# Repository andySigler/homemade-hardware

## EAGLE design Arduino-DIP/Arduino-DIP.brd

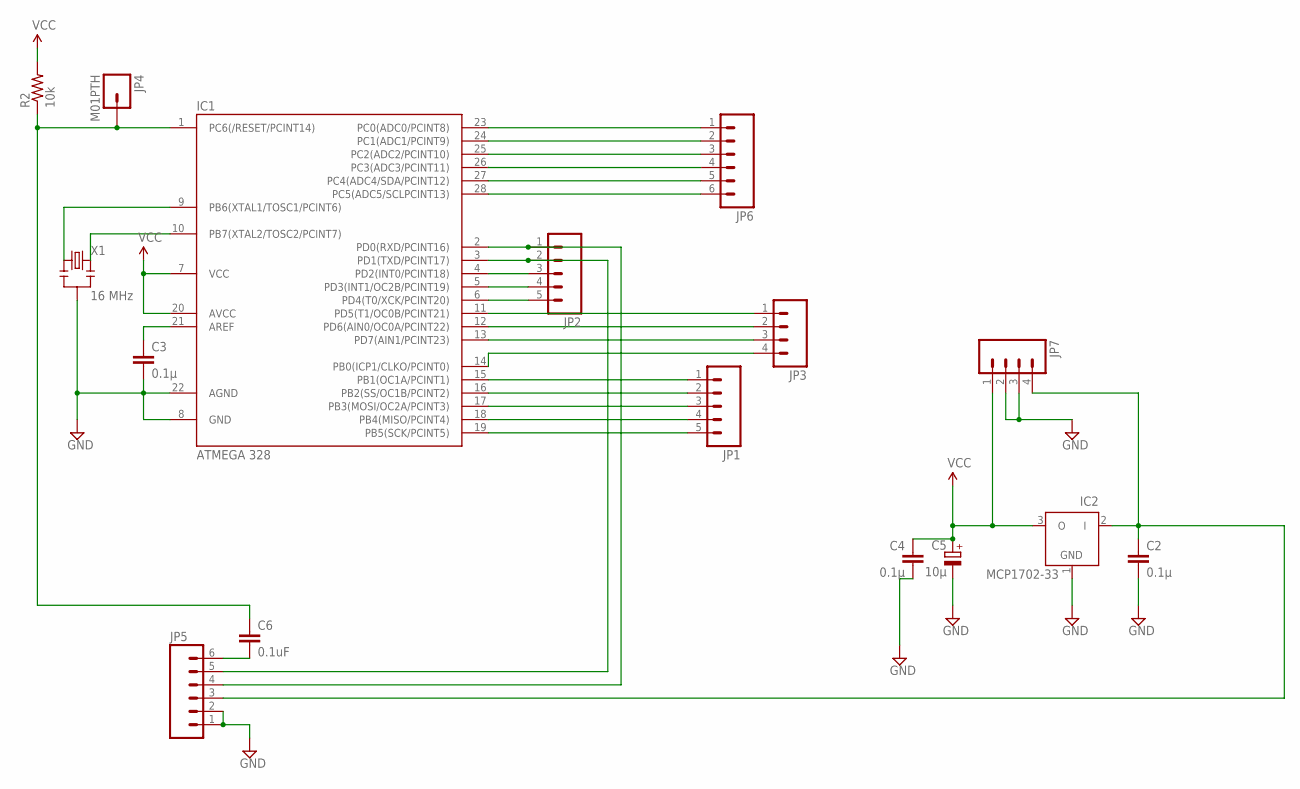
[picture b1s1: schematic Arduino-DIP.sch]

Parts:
C2, C3, C4: 0.1µ; C025-024X044
C5: 10µ; E1,8-4
C6: 0.1uF; CAP-PTH-5MM
IC1: ATMEGA 328; DIL28-3
IC2: MCP1702-33; TO92
JP1, JP2: M05PTH; 1X05
JP3, JP7: M04PTH; 1X04
JP4: M01PTH; 1X01
JP5, JP6: M06NO_SILK; 1X06_NO_SILK
R2: 10k; 1/6W-RES
X1: 16 MHz; RESONATOR-PTH

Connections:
GND: C2.2, C3.2, C4.2, C5.-, IC1.8 (GND), IC1.22 (AGND), IC2.1 (GND), JP5.1, JP5.2, JP7.2, JP7.3, X1.2
unnamed: IC1.9 (PB6(XTAL1/TOSC1/PCINT6)), X1.1
unnamed: IC1.23 (PC0(ADC0/PCINT8)), JP6.1
unnamed: IC1.24 (PC1(ADC1/PCINT9)), JP6.2
unnamed: IC1.25 (PC2(ADC2/PCINT10)), JP6.3
unnamed: IC1.26 (PC3(ADC3/PCINT11)), JP6.4
unnamed: IC1.27 (PC4(ADC4/SDA/PCINT12)), JP6.5
unnamed: IC1.28 (PC5(ADC5/SCLPCINT13)), JP6.6
unnamed: IC1.4 (PD2(INT0/PCINT18)), JP2.3
unnamed: IC1.5 (PD3(INT1/OC2B/PCINT19)), JP2.4
unnamed: IC1.6 (PD4(T0/XCK/PCINT20)), JP2.5
unnamed: IC1.11 (PD5(T1/OC0B/PCINT21)), JP3.1
unnamed: IC1.12 (PD6(AIN0/OC0A/PCINT22)), JP3.2
unnamed: IC1.13 (PD7(AIN1/PCINT23)), JP3.3
unnamed: IC1.14 (PB0(ICP1/CLKO/PCINT0)), JP3.4
unnamed: IC1.15 (PB1(OC1A/PCINT1)), JP1.1
unnamed: IC1.16 (PB2(SS/OC1B/PCINT2)), JP1.2
unnamed: IC1.17 (PB3(MOSI/OC2A/PCINT3)), JP1.3
unnamed: IC1.18 (PB4(MISO/PCINT4)), JP1.4
unnamed: C3.1, IC1.21 (AREF)
unnamed: C6.2, JP5.6
unnamed: IC1.10 (PB7(XTAL2/TOSC2/PCINT7)), X1.3
unnamed: IC1.19 (PB5(SCK/PCINT5)), JP1.5
PWR: C2.1, IC2.2 (I), JP5.3, JP7.4
RST: C6.1, IC1.1 (PC6(/RESET/PCINT14)), JP4.1, R2.1
RXD: IC1.2 (PD0(RXD/PCINT16)), JP2.1, JP5.4
TXD: IC1.3 (PD1(TXD/PCINT17)), JP2.2, JP5.5
VCC: C4.1, C5.+, IC1.7 (VCC), IC1.20 (AVCC), IC2.3 (O), JP7.1, R2.2

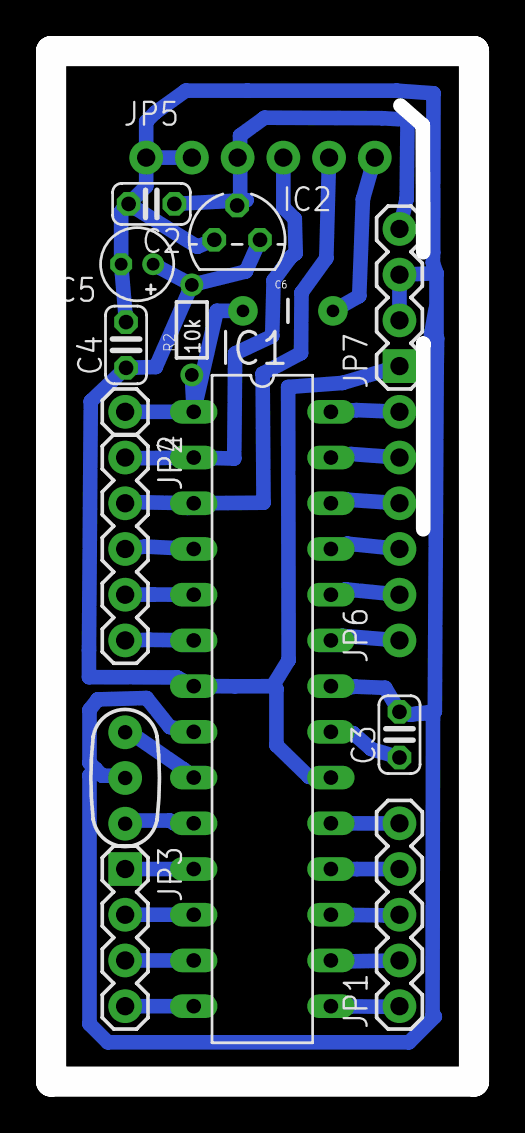
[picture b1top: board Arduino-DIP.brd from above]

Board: 2 copper layers, 23.5 x 57.3 mm, 16 parts (0 on the bottom side), 28 nets.

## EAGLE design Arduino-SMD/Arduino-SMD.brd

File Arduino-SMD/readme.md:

#Homemade SMD Microcontroller
##A clone of the Arduino-Pro-Mini

This is a redesign of the [Arduino Pro Mini](http://arduino.cc/en/Main/arduinoBoardProMini). The design is constrained by rapid prototyping tools and processes used to make the PCB. The most notabe constraints are micro-milling machines and DIY vias.

###Features

* Bootloader: Arduino Pro Mini (3.3V, 8MHz) w/ ATmega328
* Specs: 3.3 volts @ 8MHz
* Dimension: 3.5cm x 2cm (1.37" x 0.8")
* Onboard LED on Digital Pin 5 (not 13)
* FTDI programming headers
* Onboard reset button
* Solder points for [coin cell battery holder](http://www.digikey.com/product-detail/en/BA2032/BA2032-ND/257744)

###Pinouts

###Building

The board is designed to be milled on a micro-milling machine from copper clad plates. The job requires:
* 1/64" and 1/32" endmill to form routes
* 18 and 22 gauge drill bits for vias and holes
* 1/16" endmill for the dimension

Toolpath lines are drawn with the `wire` command on `.brd` layers `114`, `115`, `117`, and `118`.

Dynamask solder mask is then applied, and the board is exposed in a homemade UV lightbox for 45 seconds. This exposure is made through transparency film with the `.brd` `tStop` and `bStop` printed in black.

Vias are filled with solid 24 gauge wire, bent at 90 degree angles on either side to prevent them from falling out. Solder paste is then applied to the vias, and reflowed to make connections between the top and bottom.

###Parts List

* [ATMega328](http://www.digikey.com/product-detail/en/ATMEGA328-AUR/ATMEGA328-AURCT-ND/3440951) (this build does not use the more popular [ATMega328p](http://www.digikey.com/product-detail/en/ATMEGA328P-AUR/ATMEGA328P-AURCT-ND/3789455))
* [3.3 Volt Regulator](http://www.digikey.com/product-detail/en/MIC5205-3.3YM5%20TR/576-1259-1-ND/771886)
* [16 MHz Resonator](http://www.digikey.com/product-detail/en/PRQC16.00SR1010V00L/1253-1339-1-ND/4879394)
* [10 uF Pol. Capacitor](http://www.digikey.com/product-detail/en/T491A106K006AT7280/399-10116-1-ND/3759233) x 2
* [0.1 uF Capacitor](http://www.digikey.com/product-detail/en/CC0603ZRY5V9BB104/311-1343-1-ND/2103127) x 3
* [10,000 Ohm Resistor](http://www.digikey.com/product-detail/en/RC0603JR-0710KL/311-10KGRCT-ND/729647) x 3
* [LED](http://www.digikey.com/product-search/en?pv7=2&k=160-1434-2-ND&mnonly=0&newproducts=0&ColumnSort=0&page=1&quantity=0&ptm=0&fid=0&pageSize=25) x 2
* [Tactile Switch](http://www.digikey.com/product-detail/en/8-1437565-1/450-1941-ND/529677)
* [Coin Cell Battery Holder](http://www.digikey.com/product-detail/en/BA2032/BA2032-ND/257744) (optional)

###Burning a Bootloader

This build does not use the ATMega328p, but instead the ATMega328 because that's what I had on me. This will make the Arduino IDE unable to recognize the chip when burning a bootloader, but you can be fix it by adding a new device signature to the Arduino IDE's 'avrdude.conf' file.

The steps below will guide you through adding the device signature for the ATMega328. However, these changes must be undone in order to send sketches to the board after burning the bootloader.

#####Step 1
Quit the Arduino IDE if it is open.
#####Step 2
Find where you've installed Arduino, right-click it, and select `Show Package Contents`
#####Step 3
Navigate all the way into `Contents/Resources/Java/hardware/tools/avr/etc` and you'll find the `avrdude.conf` file
#####Step 4
Open `avrdude.conf` in a text editor, and find the following line for the ATMega328p:
```
signature   = 0x1e 0x95 0x0F;
```
#####Step 5
Comment that line out with an `#`, and add the new signature of the ATMega328. It should like like the following now:
```
# signature   = 0x1e 0x95 0x0F;
signature   = 0x1e 0x95 0x14;
```
#####Step 6
Restart the Arduino IDE, and you should be able to bootload the board.
#####Step 7
When you're done, change the `avrdude.conf` file back to it's original settings so that you can send your sketches to the board:
```
signature   = 0x1e 0x95 0x0F;
# signature   = 0x1e 0x95 0x14;
```

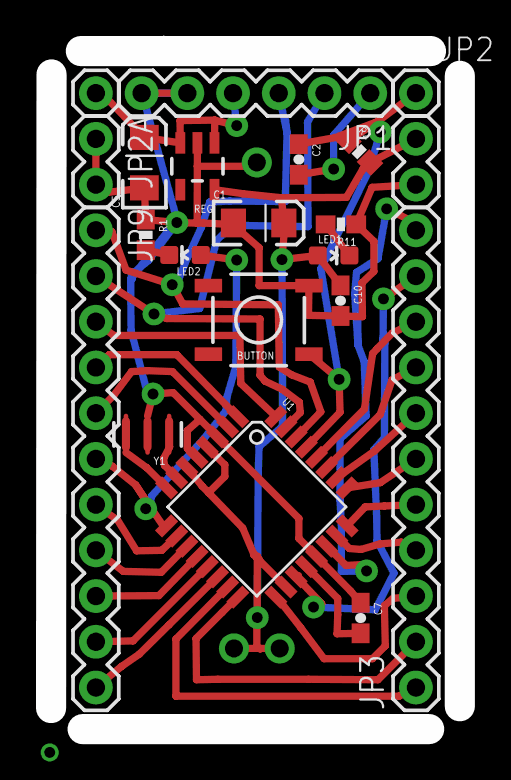
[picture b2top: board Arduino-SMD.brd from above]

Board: 2 copper layers, 22.7 x 37.7 mm, 22 parts (1 on the bottom side), 32 nets.

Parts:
BUTTON: Button; TACTILE-SWITCH-SMD
C1, C5: 10uF; EIA3216
C2, C7, C10: 0.1uF; 0603-CAP
JP1: FTDI Basic; 1X06
JP2, JP4: M01PTH; 1X01
JP2A, JP2A1: M02PTH; 1X02
JP3, JP9: M11PTH; 1X11
LED1, LED2: Red; 0603-LED-ALT1
R1, R2, R11: 10K; 0603-RES
REG: 3.3V; SOT23-5
U1: ATMEGA328P; TQFP32-08
U$1: BATTERY-ITP; BATTCOM_20MM_PTH
Y1: 8MHZ; RESONATOR-SMD

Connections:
DTR: C2.2, JP1.1
GND: BUTTON.3, C1.C, C5.C, C7.1, C10.2, JP1.5, JP1.6, JP2A.1, JP2A.2, JP2A1.2, R1.1, R11.1, REG.2, U1.3, U1.5, U1.21, U$1.GND, Y1.2
unnamed: U1.8, Y1.3
unnamed: U1.7, Y1.1
unnamed: LED1.C, R11.2
unnamed: JP3.1, U1.15
unnamed: JP3.2, U1.16
unnamed: JP3.3, U1.17
unnamed: JP3.11, U1.22
unnamed: JP3.10, U1.19
unnamed: JP3.9, U1.28
unnamed: JP3.8, U1.27
unnamed: JP3.7, U1.26
unnamed: JP3.6, U1.25
unnamed: JP3.5, U1.24
unnamed: JP3.4, U1.23
unnamed: LED2.C, R1.2
unnamed: JP9.7, U1.10
unnamed: C5.A, JP1.4, JP4.1, REG.1, REG.3
unnamed: JP9.3, U1.32
unnamed: C7.2, U1.20
unnamed: JP9.4, U1.1
unnamed: JP9.5, U1.2
unnamed: JP9.6, LED2.A, U1.9
unnamed: JP9.8, U1.11
unnamed: JP9.9, U1.12
unnamed: JP9.10, U1.13
unnamed: JP9.11, U1.14
RESET: BUTTON.1, C2.1, JP2.1, R2.1, U1.29
RXI: JP1.3, JP9.1, U1.30
TXO: JP1.2, JP9.2, U1.31
VCC: C1.A, C10.1, JP2A1.1, LED1.A, R2.2, REG.5, U1.4, U1.6, U1.18, U$1.PWR, U$1.PWR2

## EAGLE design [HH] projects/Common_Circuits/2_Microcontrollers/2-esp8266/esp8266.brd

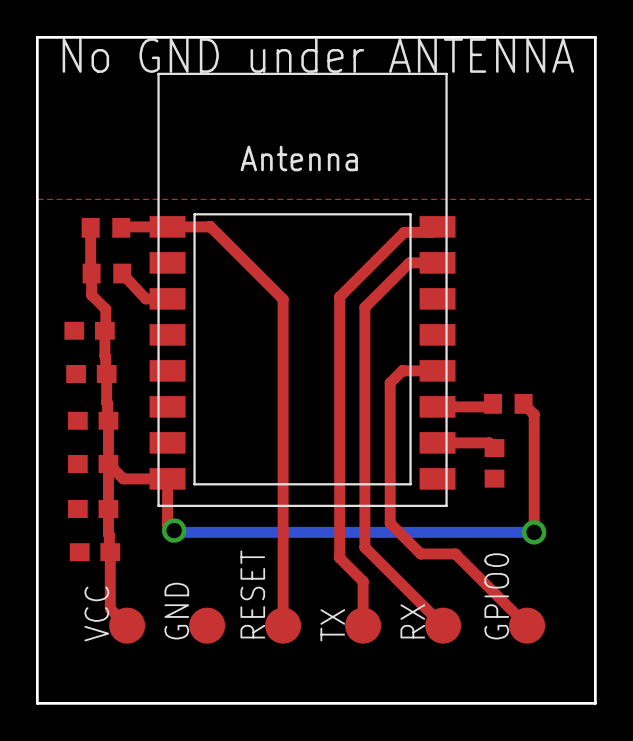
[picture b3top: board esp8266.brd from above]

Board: 2 copper layers, 31.0 x 37.0 mm, 17 parts (0 on the bottom side), 9 nets.

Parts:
C1, C6: 0.1uF; 0603
C2, C3, C4, C5: 4.7uF; 0603
GND: TPTP20R; TP20R
GPIO0: TPTP20R; TP20R
R3, R5, R8, R9: 10k; R0603
RESET: TPTP20R; TP20R
RX: TPTP20R; TP20R
TX: TPTP20R; TP20R
VCC: TPTP20R; TP20R
X1: ESP-12

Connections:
CH_PD: R8.1, X1.3
GND: C1.2, C2.2, C3.2, C4.2, C5.2, C6.2, GND.TP, R9.1, X1.9
GPIO0: GPIO0.TP, X1.12
GPIO2: R5.1, X1.11
GPIO15: R9.2, X1.10
RESET: R3.1, RESET.TP, X1.1
RXD: RX.TP, X1.15
TXD: TX.TP, X1.16
VCC: C1.1, C2.1, C3.1, C4.1, C5.1, C6.1, R3.2, R5.2, R8.2, VCC.TP, X1.8

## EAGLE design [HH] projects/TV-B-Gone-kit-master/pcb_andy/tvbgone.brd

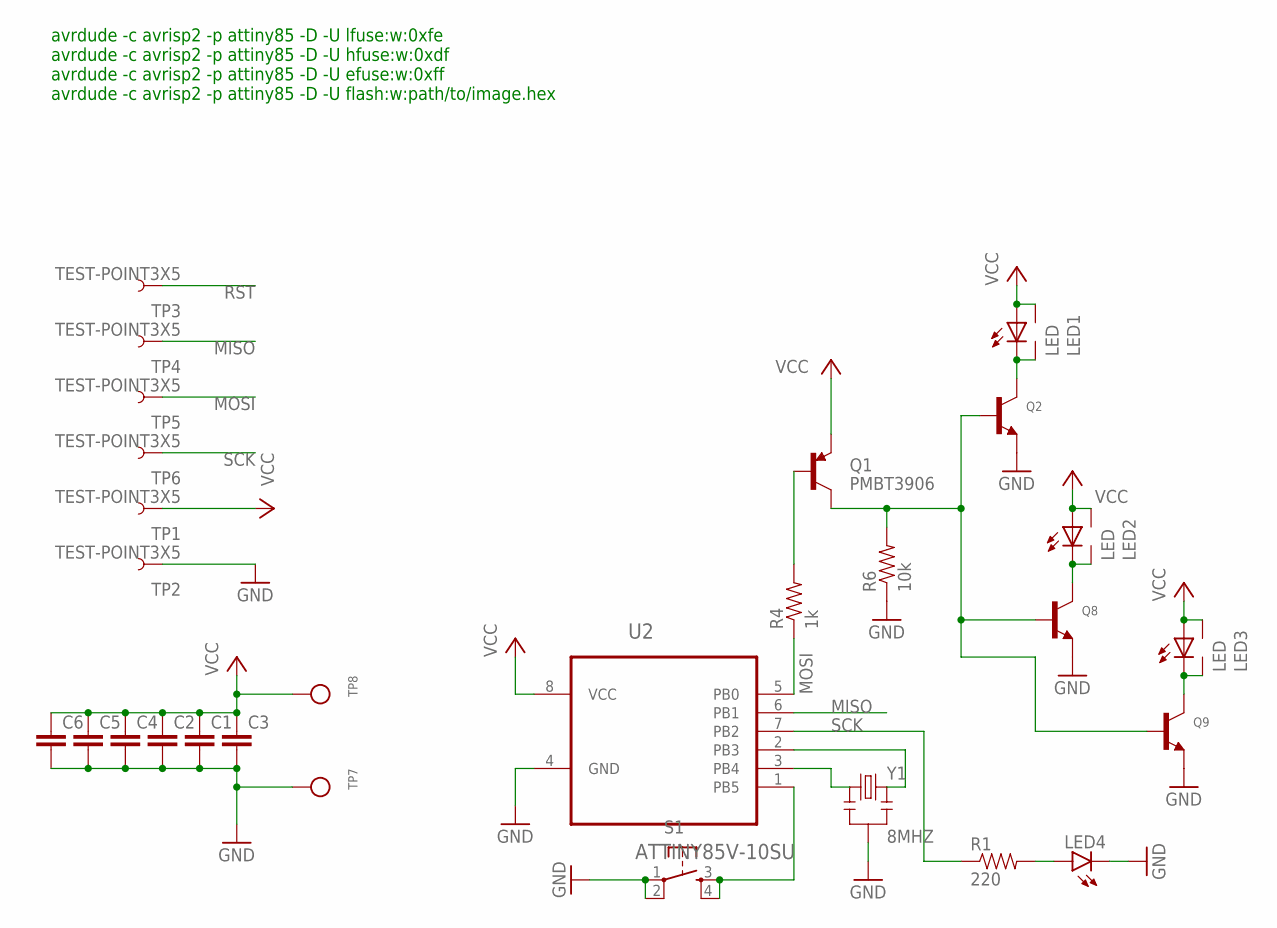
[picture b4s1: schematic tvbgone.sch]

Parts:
C1, C2, C3, C4, C5, C6: CAP0603-CAP; 0603-CAP
LED1, LED2, LED3: LED; 5MM-SIDE
LED4: LED0603; LED-0603
Q1: PMBT3906; SOT23-3
Q2, Q8, Q9: TRANSISTOR_NPN; SOT-23-R
R1: 220; 0603-RES
R4: 1k; 0603-RES
R6: 10k; 0603-RES
S1: TAC_SWITCHSMD; TACTILE-SWITCH-SMD
TP1, TP2, TP3, TP4, TP5, TP6: TEST-POINT3X5; PAD.03X.05
TP7, TP8: TESTPOINTPAD; TESTPOINT_PAD_2MM
U2: ATTINY85V-10SU; SOIC127P798X216-8N
Y1: 8MHZ; RESONATOR-SMD

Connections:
GND: C1.2, C2.2, C3.2, C4.2, C5.2, C6.2, LED4.C, Q2.3-EMITTER (E), Q8.3-EMITTER (E), Q9.3-EMITTER (E), R6.1, S1.1, S1.2, TP2.P$1, TP7.P$1, U2.4 (GND), Y1.2
MISO: TP4.P$1, U2.6 (PB1)
MOSI: R4.1, TP5.P$1, U2.5 (PB0)
unnamed: U2.3 (PB4), Y1.1
unnamed: U2.2 (PB3), Y1.3
unnamed: LED4.A, R1.2
unnamed: LED1.K (C), LED1.K2 (C1), Q2.2-COLLECTOR (C)
unnamed: LED2.K (C), LED2.K2 (C1), Q8.2-COLLECTOR (C)
unnamed: Q1.1 (B), R4.2
unnamed: LED3.K (C), LED3.K2 (C1), Q9.2-COLLECTOR (C)
unnamed: Q1.3 (C), Q2.1-BASE (B), Q8.1-BASE (B), Q9.1-BASE (B), R6.2
RST: S1.3, S1.4, TP3.P$1, U2.1 (PB5)
SCK: R1.1, TP6.P$1, U2.7 (PB2)
VCC: C1.1, C2.1, C3.1, C4.1, C5.1, C6.1, LED1.A, LED1.A2 (A1), LED2.A, LED2.A2 (A1), LED3.A, LED3.A2 (A1), Q1.2 (E), TP1.P$1, TP8.P$1, U2.8 (VCC)

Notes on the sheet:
avrdude -c avrisp2 -p attiny85 -D -U lfuse:w:0xfe avrdude -c avrisp2 -p attiny85 -D -U hfuse:w:0xdf avrdude -c avrisp2 -p attiny85 -D -U efuse:w:0xff avrdude -c avrisp2 -p attiny85 -D -U flash:w:path/to/image.hex

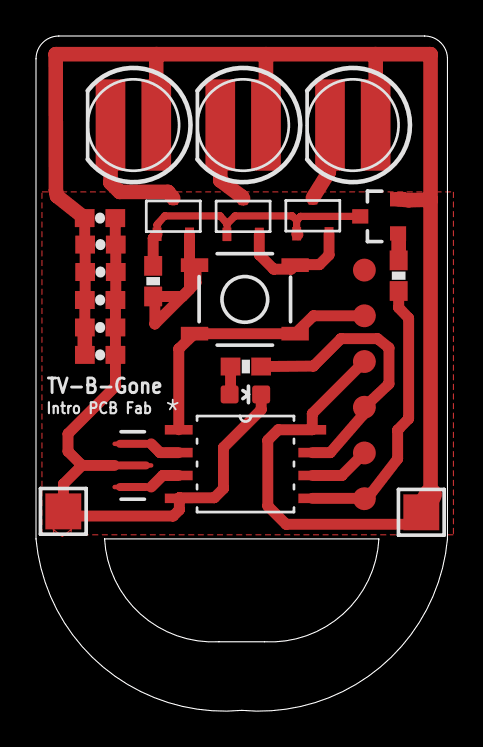
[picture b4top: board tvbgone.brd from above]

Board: 2 copper layers, 22.9 x 37.5 mm, 28 parts (0 on the bottom side), 14 nets.

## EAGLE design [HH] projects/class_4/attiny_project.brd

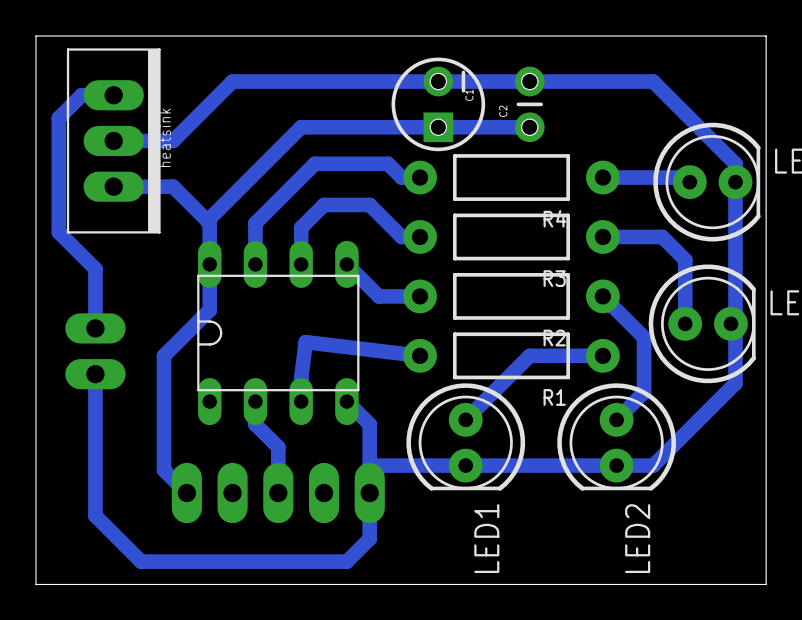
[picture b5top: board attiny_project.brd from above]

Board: 2 copper layers, 40.6 x 30.5 mm, 14 parts (0 on the bottom side), 12 nets.

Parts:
C1: CPOL-RADIAL-10UF-25V
C2: CAP-PTH-SMALL
LED1, LED2, LED3, LED4: LED5MM
R1, R2, R3, R4: AXIAL-0.4
U$1: SOCKET-8PINDIP; SOCKET-8PIN
U$2: HEADER-5
U$3: REGULATOR5V-MC7805CT; REGULATOR-7805
U$4: HEADER-2

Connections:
GND: C1.2, C2.2, LED1.K, LED2.K, LED3.K, LED4.K, U$1.4, U$2.1, U$3.GND, U$4.1
LED1: R1.P$2, U$1.3
LED2: R2.P$2, U$1.5
LED3: R3.P$2, U$1.6
LED4: R4.P$2, U$1.7
unnamed: U$3.INPUT, U$4.2
unnamed: LED1.A, R1.P$1
unnamed: LED2.A, R2.P$1
unnamed: LED3.A, R3.P$1
unnamed: LED4.A, R4.P$1
POT: U$1.2, U$2.3
VCC: C1.1, C2.1, U$1.8, U$2.5, U$3.OUTPUT

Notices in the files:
parts and their libraries:
SparkFun-Connectors: Licensing: CC v3.0 Share-Alike You are welcome to use this library for commercial purposes.
SparkFun-Passives: Licensing: Creative Commons ShareAlike 4.0 International - https://creativecommons.org/licenses/by-sa/4.0
